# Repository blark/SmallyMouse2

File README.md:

# A1200 SmallyMouse2

**This is a FORK of the original SmallyMouse2 for the Amiga 1200 Rev 2B motherboard!**

## Synopsis

SmallyMouse2 is the AT90USB1287 firmware source code and KiCAD schematic/PCB design for the SmallyMouse2 project.

## Motivation

SmallyMouse2 is a project that creates a USB mouse adaptor for retro computers that use quadrature mouse input including the Acorn BBC Micro, Acorn Master series, Commodore Amiga, Atari ST, busmouse compatible computers and many more.  SmallyMouse2 provides both a generic mouse output header (for attaching mouse to retro computer cables) and an IDC connector suitable for use with Acorn 8-bit user-ports.  SmallyMouse2 also features a configurable quadrature rate limiter that prevents VIA overrun when in use with slower 8-bit machines.

SmallyMouse2 supports both JTAG and USB bootloader programming.  The AT90USB1287 is pre-programmed by Atmel with the (FLIP) DFU bootloader; this bootloader is recognised by Atmel Studio as a programming device and can be used to flash the firmware to the board.

## Installation

Note: This is an Atmel Studio 7 project that can be loaded and compiled by the IDE

Please see http://www.waitingforfriday.com/?p=827 for detailed documentation about SmallyMouse2

## Author

SmallyMouse2 is written and maintained by Simon Inns.

## License (Software)

    SmallyMouse2 is free software: you can redistribute it and/or modify
    it under the terms of the GNU General Public License as published by
    the Free Software Foundation, either version 3 of the License, or
    (at your option) any later version.

    SmallyMouse2 is distributed in the hope that it will be useful,
    but WITHOUT ANY WARRANTY; without even the implied warranty of
    MERCHANTABILITY or FITNESS FOR A PARTICULAR PURPOSE.  See the
    GNU General Public License for more details.

    You should have received a copy of the GNU General Public License
    along with SmallyMouse2. If not, see <http://www.gnu.org/licenses/>.

## License (Hardware)

Both the schematic and the PCB design of SmallyMouse2 (i.e. the KiCAD project and files) are covered by a Creative Commons license; as with the software you are welcome (and encouraged!) to extend, re-spin and otherwise use and modify the design as allowed by the license.  However; under the terms of the Attribution-ShareAlike 4.0 International (CC BY-SA 4.0) license you are required to release your design (or redesign) under the same license.  For details of the licensing requirements please see <https://creativecommons.org/licenses/by-sa/4.0/>

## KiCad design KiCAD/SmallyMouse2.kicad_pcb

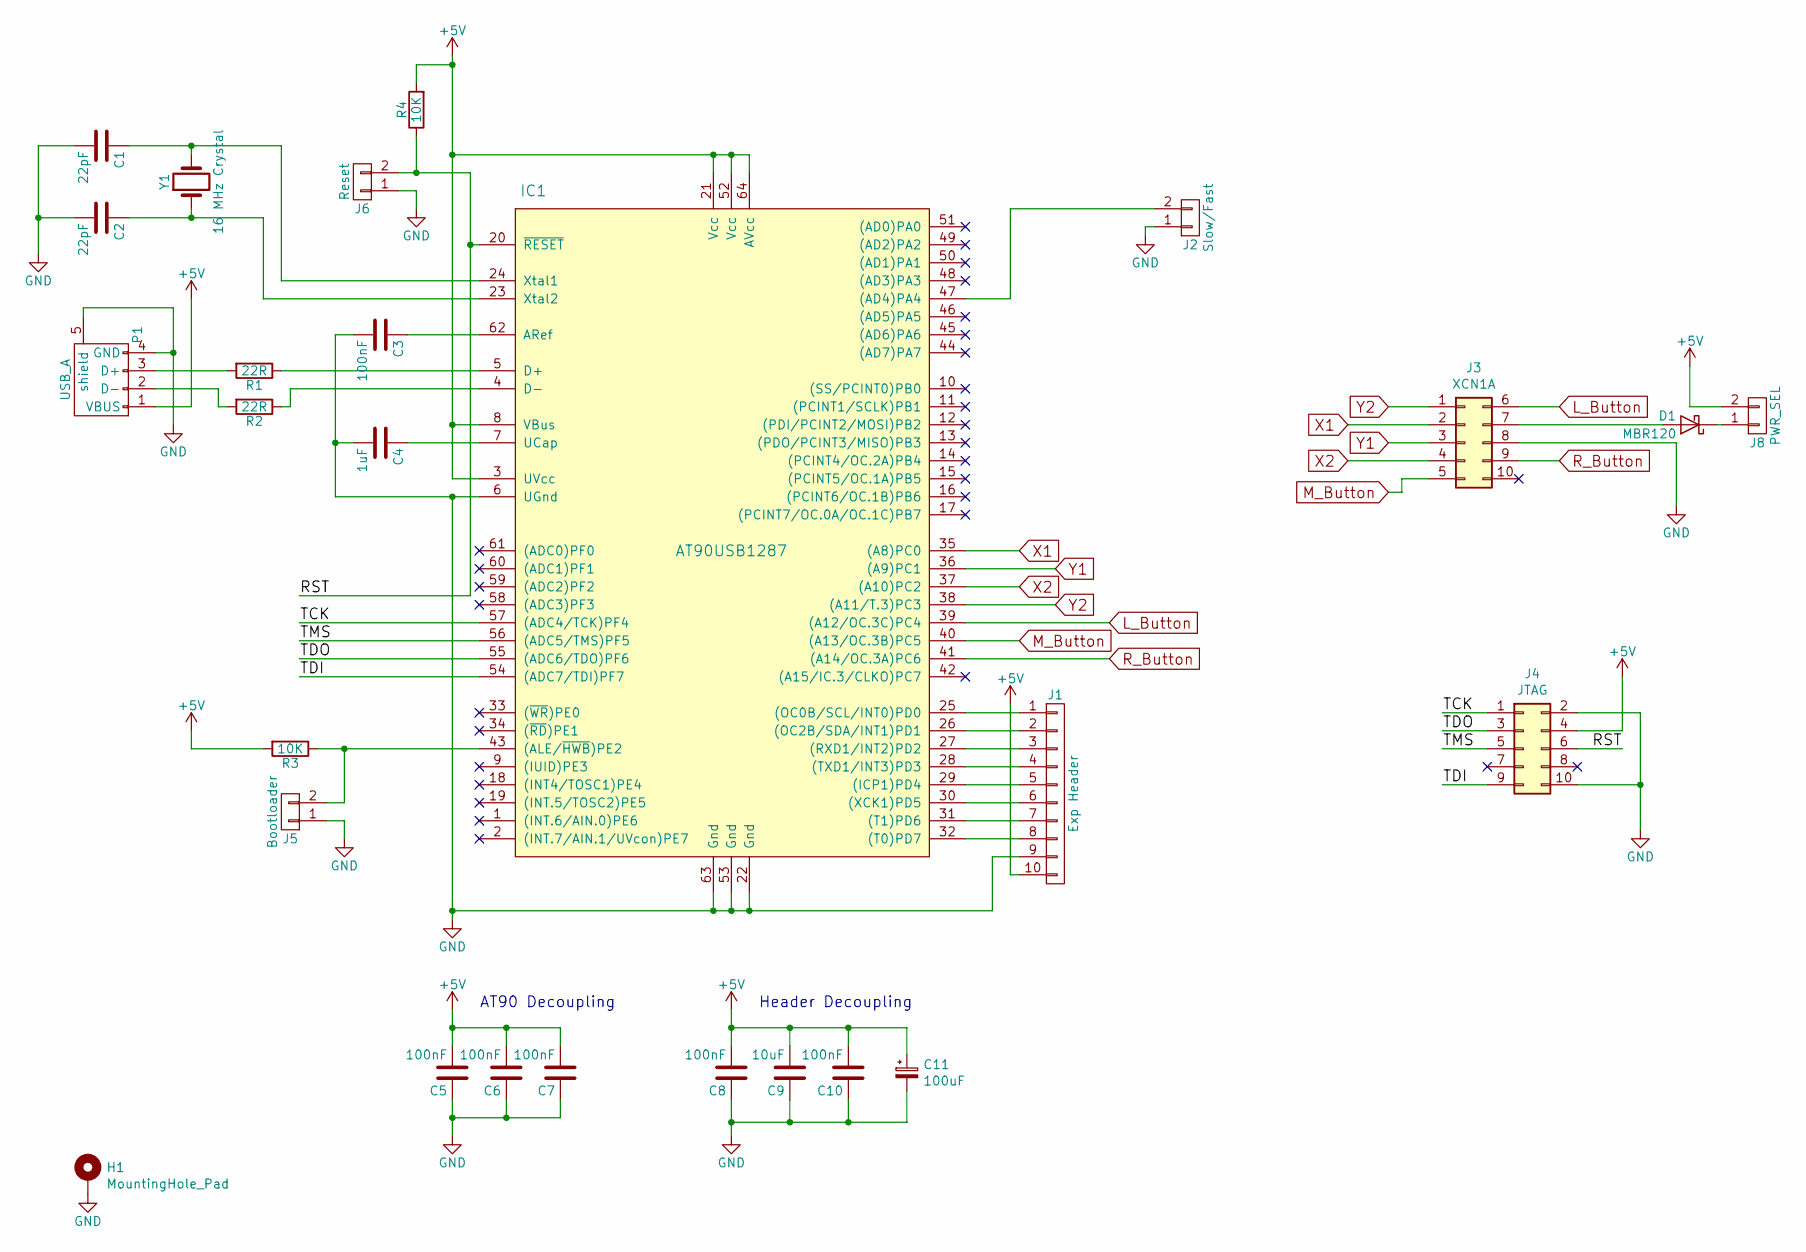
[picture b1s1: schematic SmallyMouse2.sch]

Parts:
C1, C2: 22pF; C_0805_2012Metric_Pad1.15x1.40mm_HandSolder
C3, C5, C6, C7, C8, C10: 100nF; C_0805_2012Metric_Pad1.15x1.40mm_HandSolder
C4: 1uF; C_0805_2012Metric_Pad1.15x1.40mm_HandSolder
C9: 10uF; C_0805_2012Metric_Pad1.15x1.40mm_HandSolder
C11: 100uF; CP_Radial_D5.0mm_P2.50mm
D1: MBR120; D_SOD-123F
H1: MountingHole_Pad; MountingHole_3.2mm_M3_Pad_Via
IC1: AT90USB1287; TQFP-64_14x14mm_P0.8mm
J1: Exp Header; PinHeader_1x10_P2.54mm_Vertical
J2: Slow/Fast; PinHeader_1x02_P2.54mm_Vertical
J3: XCN1A; PinHeader_2x05_P2.54mm_Horizontal
J4: JTAG; PinHeader_2x05_P2.54mm_Vertical
J5: Bootloader; PinHeader_1x02_P2.54mm_Vertical
J6: Reset; PinHeader_1x02_P2.54mm_Vertical
J8: PWR_SEL; PinHeader_1x02_P2.54mm_Vertical
P1: USB_A; USB_A_Stewart_SS-52100-001_Horizontal
R1, R2: 22R; R_0805_2012Metric_Pad1.15x1.40mm_HandSolder
R3, R4: 10K; R_0805_2012Metric_Pad1.15x1.40mm_HandSolder
Y1: 16 MHz Crystal; Crystal_SMD_HC49-SD

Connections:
+5V: C5.2, C6.2, C7.2, C8.2, C9.2, C10.2, C11.1, IC1.3 (UVcc), IC1.8 (VBus), IC1.21 (Vcc), IC1.52 (Vcc), IC1.64 (AVcc), J1.10, J4.4, J8.2, P1.1 (VBUS), R3.2, R4.2
/RST: IC1.20 (~RESET), J4.6, J6.2, R4.1
/TCK: IC1.57 ((ADC4/TCK)PF4), J4.1
/TDI: IC1.54 ((ADC7/TDI)PF7), J4.9
/TDO: IC1.55 ((ADC6/TDO)PF6), J4.3
/TMS: IC1.56 ((ADC5/TMS)PF5), J4.5
GND: C1.2, C2.2, C3.2, C4.2, C5.1, C6.1, C7.1, C8.1, C9.1, C10.1, C11.2, H1.1, IC1.6 (UGnd), IC1.22 (Gnd), IC1.53 (Gnd), IC1.63 (Gnd), J1.9, J2.1, J3.8, J4.2, J4.10, J5.1, J6.1, P1.4 (GND), P1.5 (shield)
L_Button: IC1.39 ((A12/OC.3C)PC4), J3.6
M_Button: IC1.40 ((A13/OC.3B)PC5), J3.5
unnamed: C1.1, IC1.24 (Xtal1), Y1.2
unnamed: C2.1, IC1.23 (Xtal2), Y1.1
unnamed: C3.1, IC1.62 (ARef)
unnamed: C4.1, IC1.7 (UCap)
unnamed: D1.1 (K), J8.1
unnamed: D1.2 (A), J3.7
unnamed: IC1.4 (D-), R2.1
unnamed: IC1.5 (D+), R1.1
unnamed: IC1.25 ((OC0B/SCL/INT0)PD0), J1.1
unnamed: IC1.26 ((OC2B/SDA/INT1)PD1), J1.2
unnamed: IC1.27 ((RXD1/INT2)PD2), J1.3
unnamed: IC1.28 ((TXD1/INT3)PD3), J1.4
unnamed: IC1.29 ((ICP1)PD4), J1.5
unnamed: IC1.30 ((XCK1)PD5), J1.6
unnamed: IC1.31 ((T1)PD6), J1.7
unnamed: IC1.32 ((T0)PD7), J1.8
unnamed: IC1.43 ((ALE/~HWB~)PE2), J5.2, R3.1
unnamed: IC1.47 ((AD4)PA4), J2.2
unnamed: P1.2 (D-), R2.2
unnamed: P1.3 (D+), R1.2
R_Button: IC1.41 ((A14/OC.3A)PC6), J3.9
X1: IC1.35 ((A8)PC0), J3.2
X2: IC1.37 ((A10)PC2), J3.4
Y1: IC1.36 ((A9)PC1), J3.3
Y2: IC1.38 ((A11/T.3)PC3), J3.1

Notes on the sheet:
AT90 Decoupling
Header Decoupling

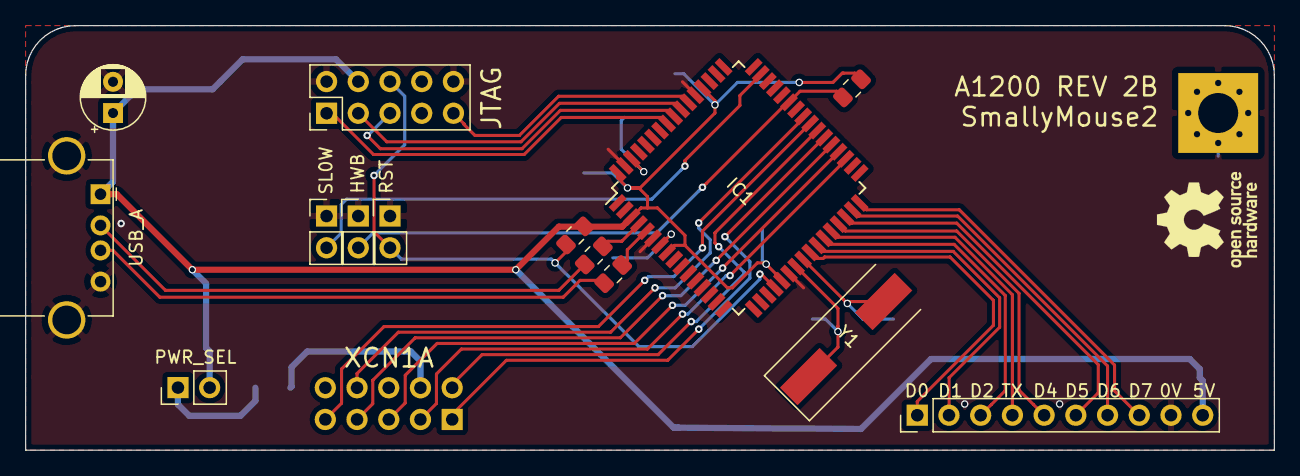
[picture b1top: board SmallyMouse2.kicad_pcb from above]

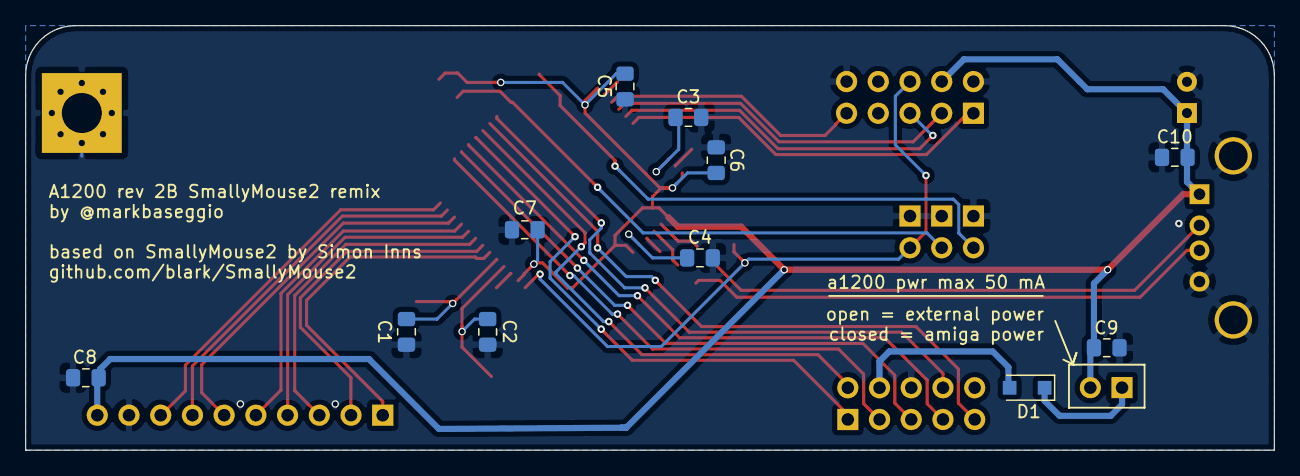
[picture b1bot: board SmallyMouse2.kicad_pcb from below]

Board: 2 copper layers, 100.0 x 34.0 mm, 27 parts (11 on the bottom side), 34 nets.

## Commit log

2020-01-25 first commit A1200 smallymouse2
2020-01-25 added note and image
2020-01-25 oops
2020-01-25 tweaks
2020-01-25 front and back
2020-01-25 front/back
2020-01-25 render fix

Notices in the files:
KiCAD/SmallyMouse2.kicad_pcb:
(c)2017 Simon Inns
License: Attribution-ShareAlike 4.0 International (CC BY-SA 4.0)
